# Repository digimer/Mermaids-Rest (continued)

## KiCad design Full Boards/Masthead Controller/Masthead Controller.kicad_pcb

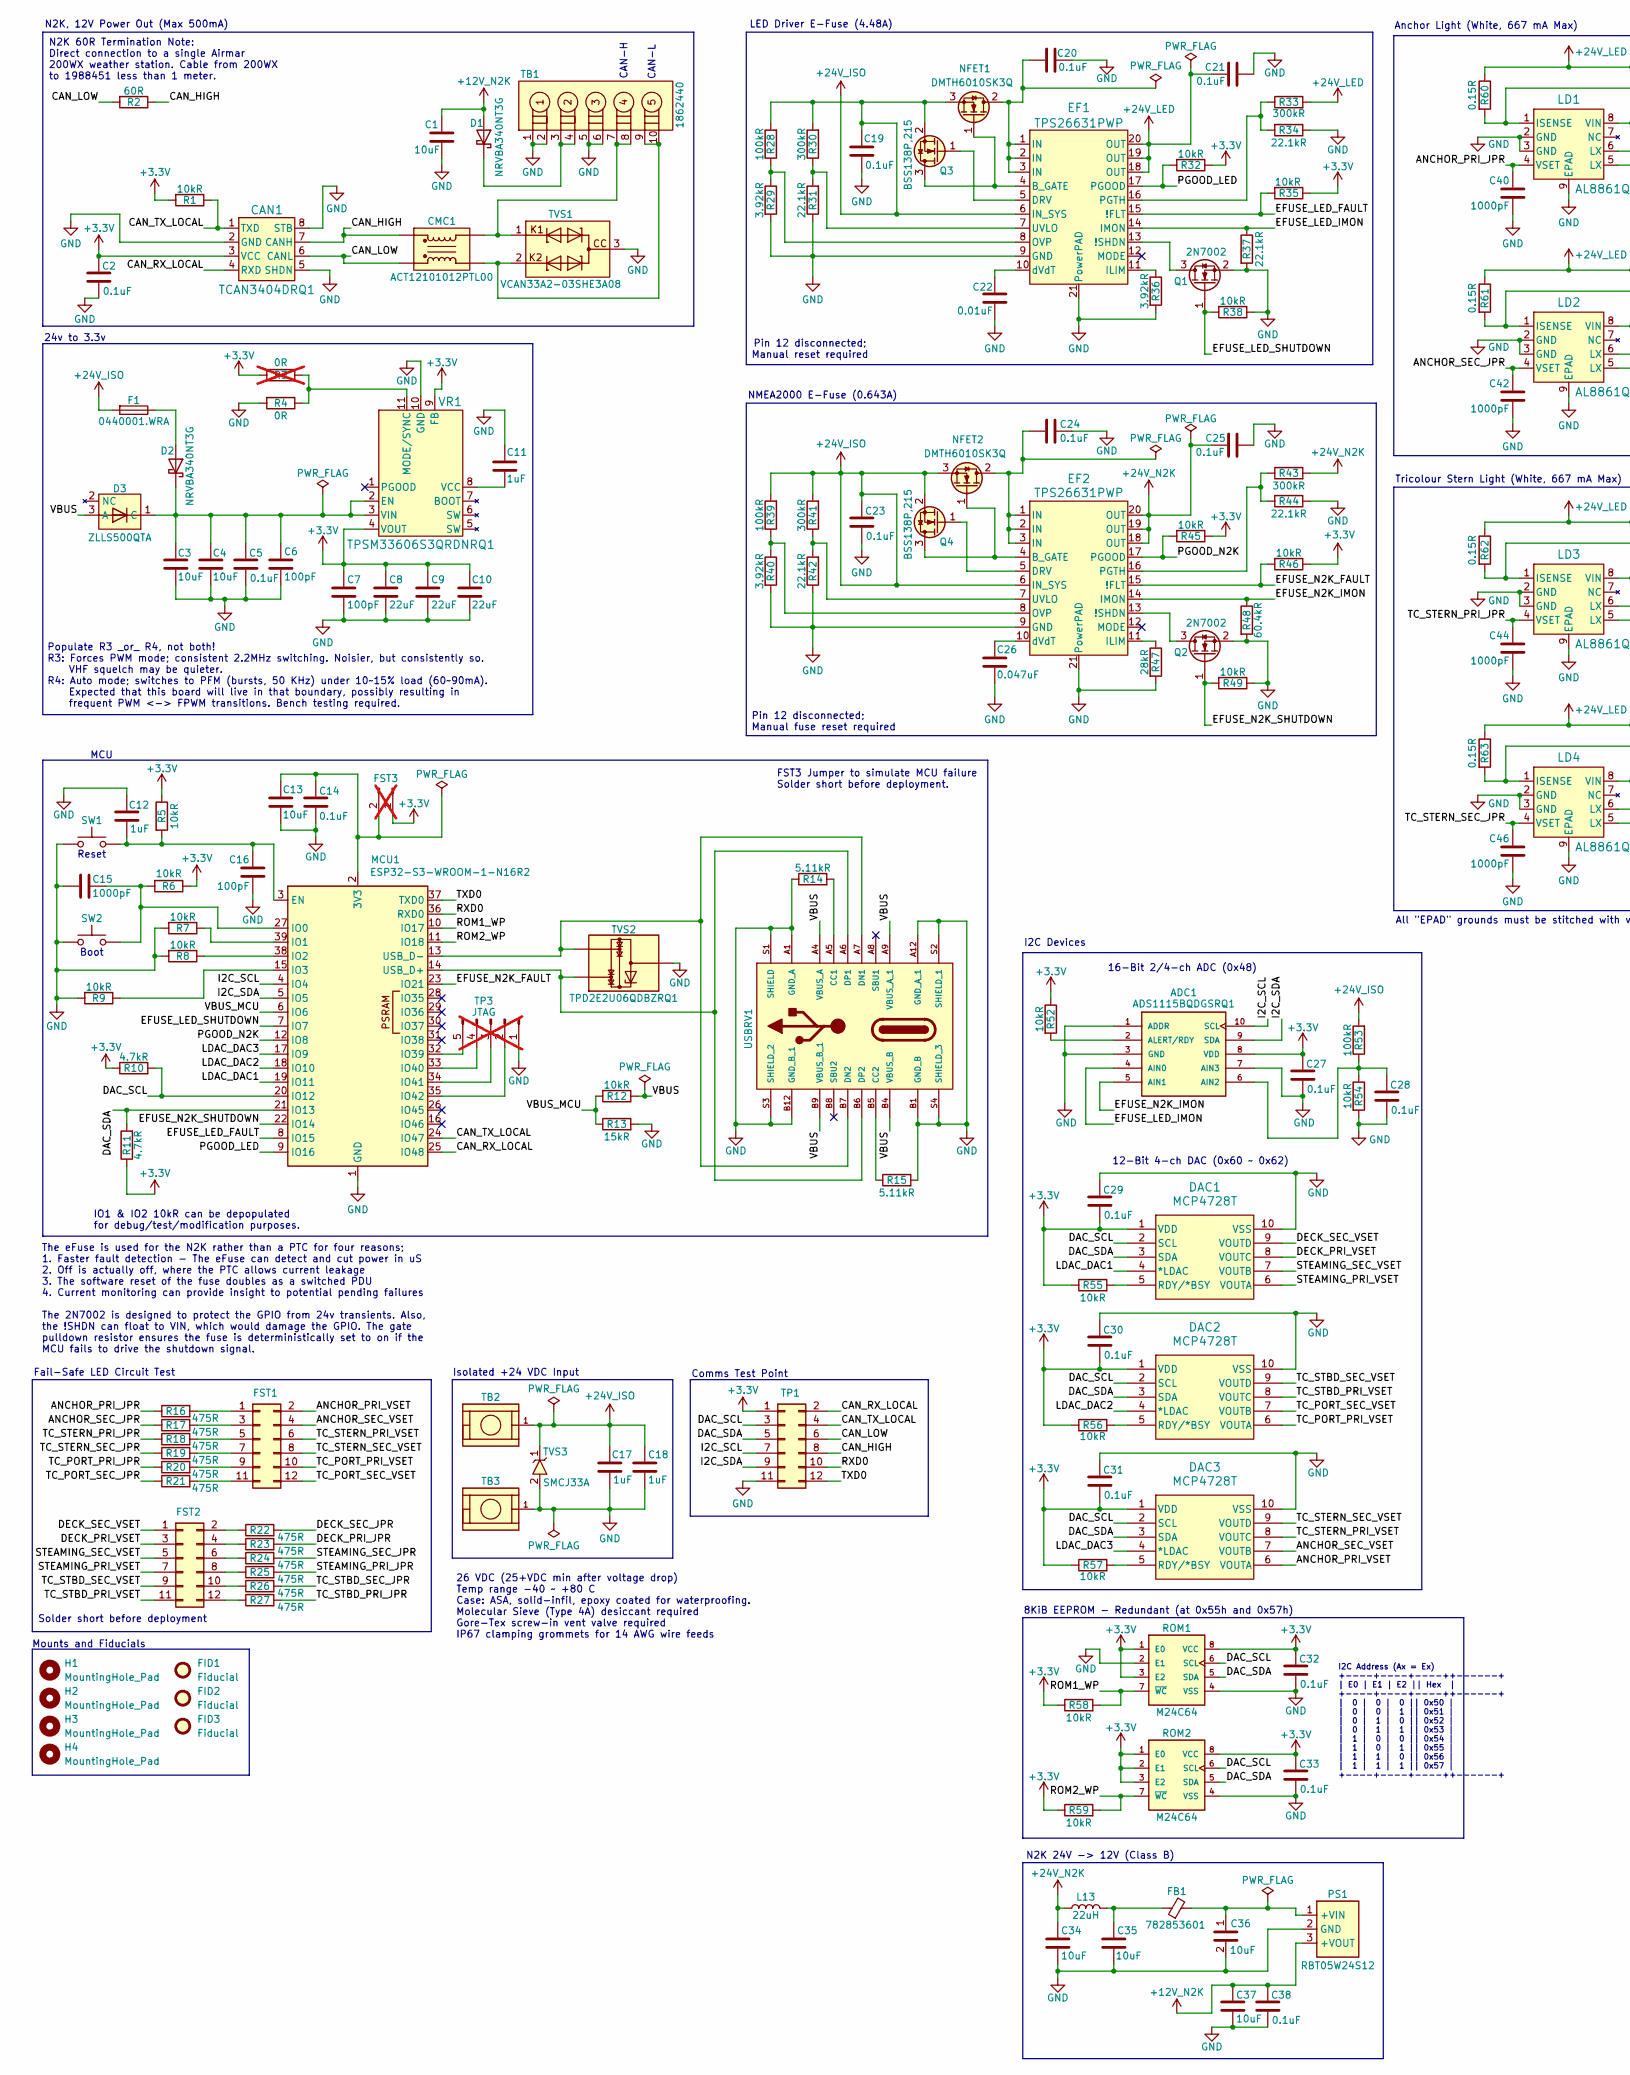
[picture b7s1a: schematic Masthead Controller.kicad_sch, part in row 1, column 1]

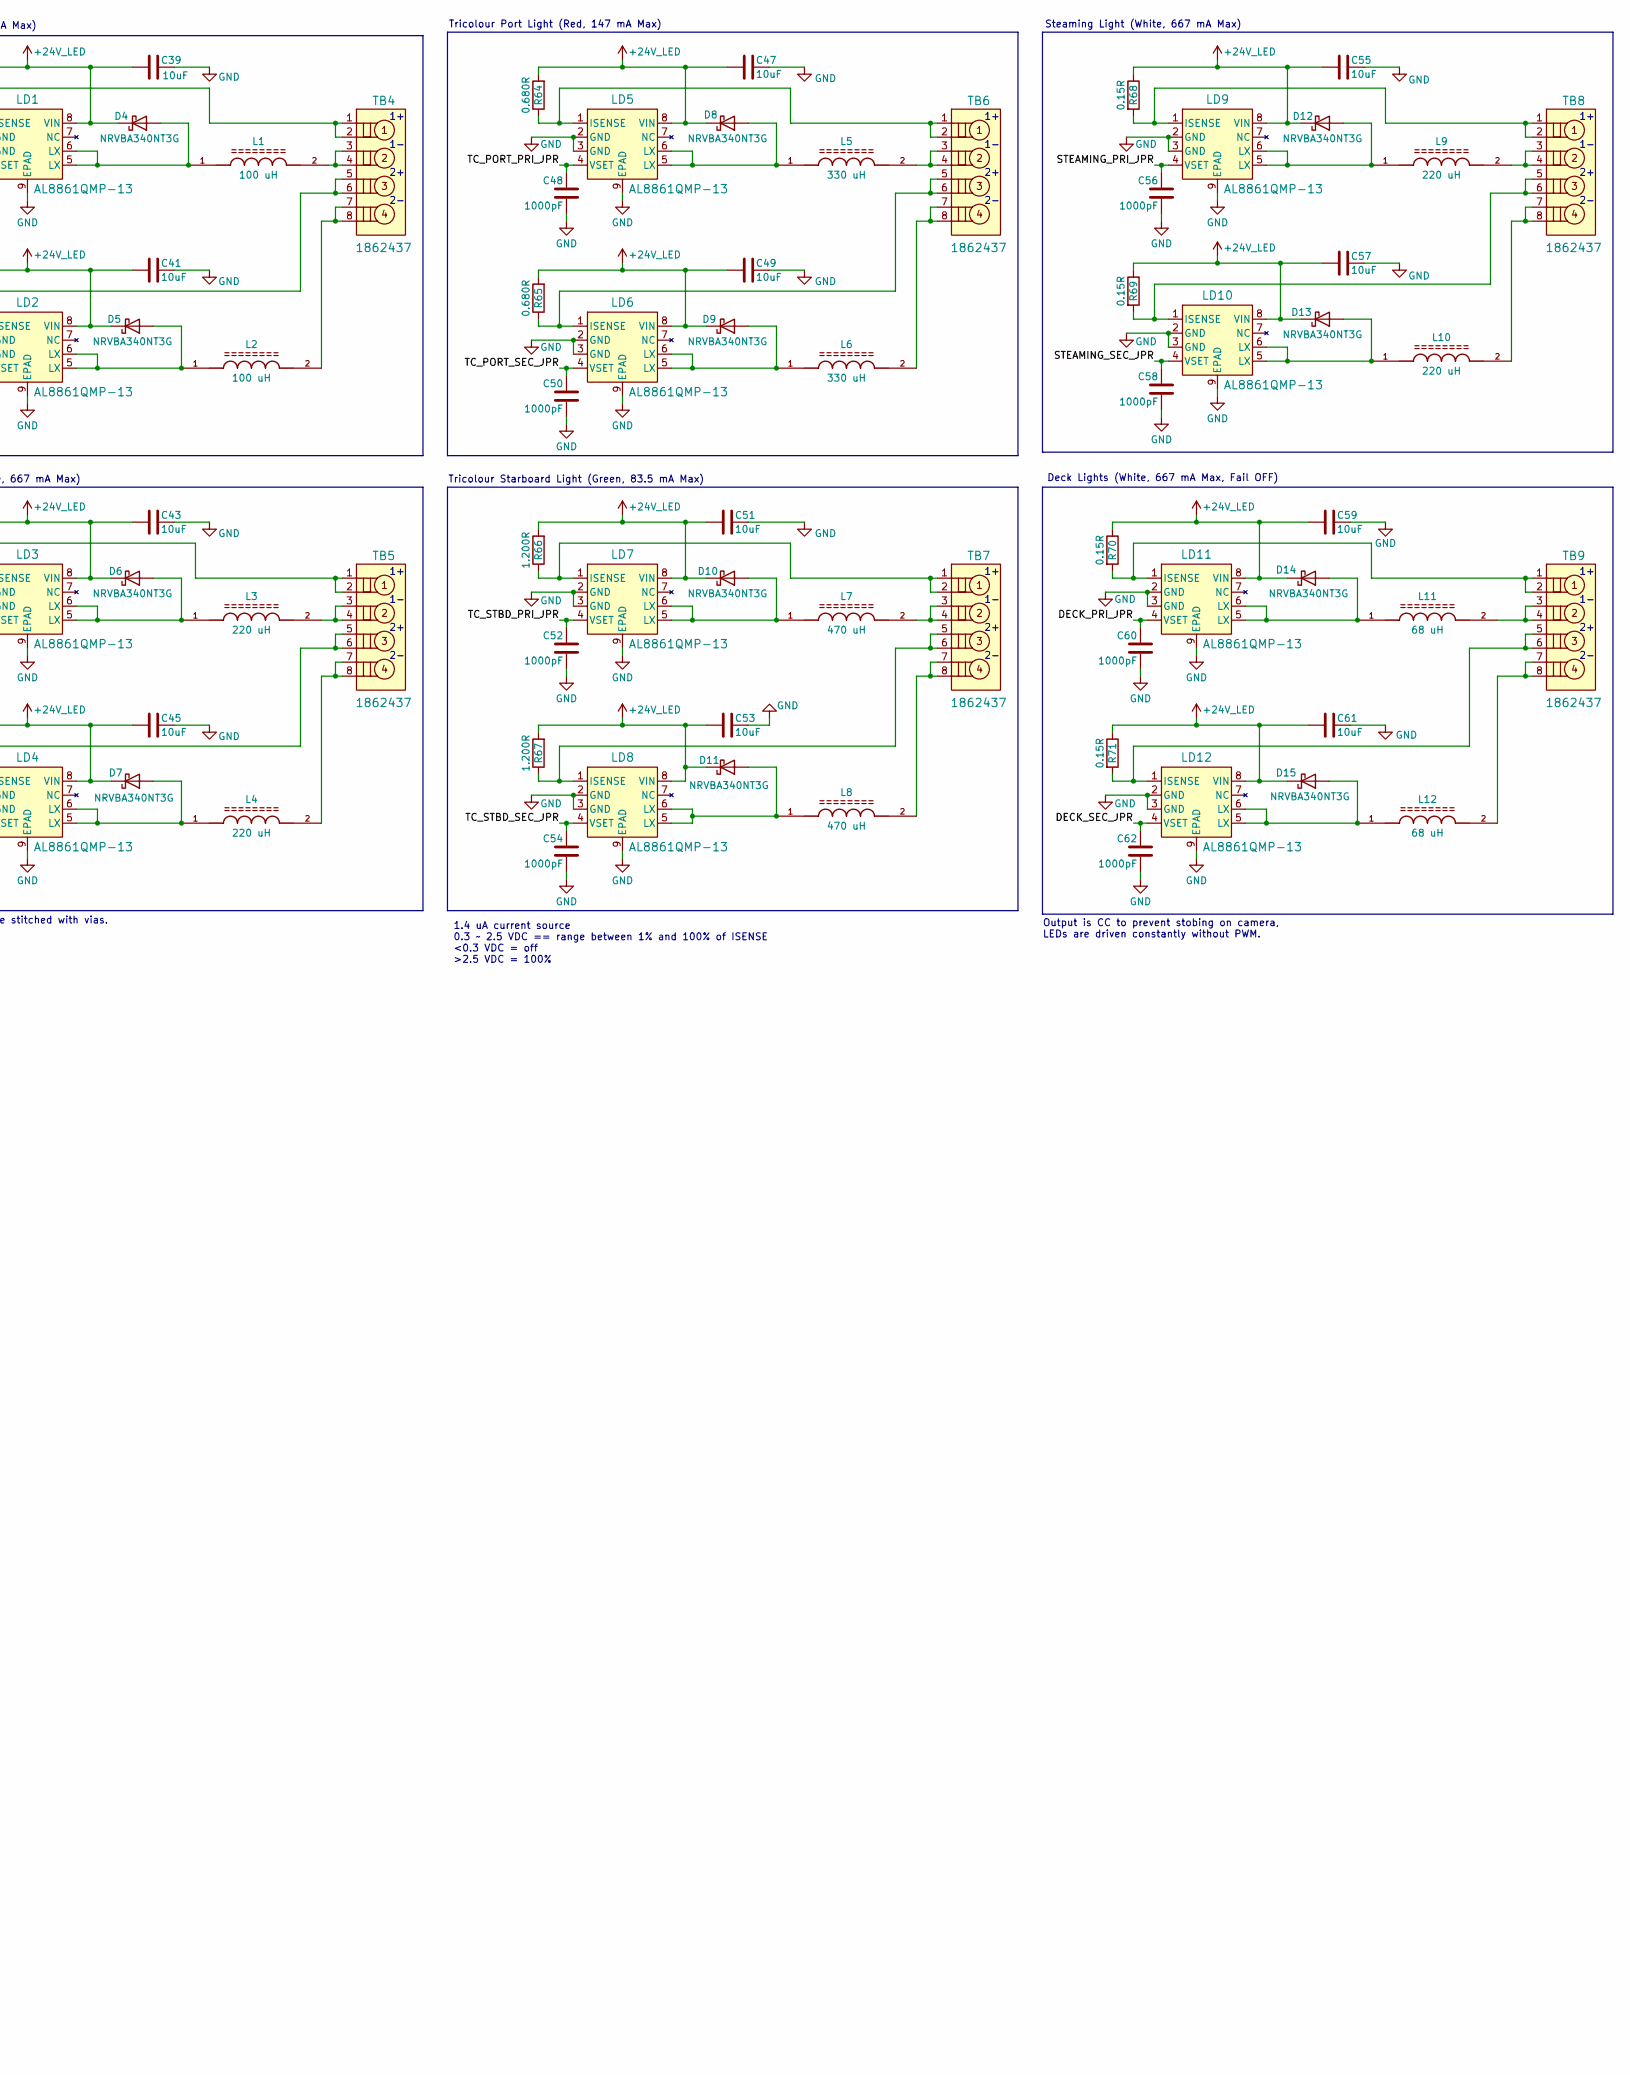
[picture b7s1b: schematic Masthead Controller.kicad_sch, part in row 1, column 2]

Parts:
ADC1: ADS1115BQDGSRQ1; TI ADS1115BQDGSRQ1; Part TI ADS1115BQDGSRQ1
C1, C3, C4, C13, C34, C35, C36, C37, C39, C41, C43, C45, C47, C49, C51, C53, C55, C57, C59, C61: 10uF; TDK CGA5; Part TDK CGA5L1X7R1H106K160AE
C2, C5, C14, C19, C20, C21, C23, C24, C25, C27, C28, C29, C30, C31, C32, C33, C38: 0.1uF; Kyocera AVX 0805; Part Kyocera 08051C104K4Z2A
C6, C7, C16: 100pF; Kemet C0805X; Part Kemet C0805X101J5GACAUTO
C8, C9, C10: 22uF; Murata GCJ32ER71C; Part Murata GCJ32ER71C226KE01L
C11, C12, C17, C18: 1uF; Kyocera AVX 0805; Part Kyocera 08051C105K4Z2A
C15, C40, C42, C44, C46, C48, C50, C52, C54, C56, C58, C60, C62: 1000pF; Kyocera AVX 0805; Part Kyocera 08052C102J4Z2A
C22: 0.01uF; Kyocera AVX 0805; Part Kyocera 08051C103J4Z2A
C26: 0.047uF; Murata GCJ 0805; Part Murata GCJ21BR72A473KA01L
CAN1: TCAN3404DRQ1; TI TCAN3404; Part TI TCAN3404DRQ1
CMC1: ACT12101012PTL00; TDK ACT12101012PTL00; Part TDK ACT1210-101-2P-TL00
D1, D2, D4, D5, D6, D7, D8, D9, D10, D11, D12, D13, D14, D15: NRVBA340NT3G; Onsemi NRVBA340NT3G; Part Onsemi NRVBA340NT3G
D3: ZLLS500QTA; Diodes Inc ZLLS500; Part Diodes Inc ZLLS500QTA
DAC1, DAC2, DAC3: MCP4728T; MT MCP4728T-E_UN; Part Microchip MCP4728T-E/UN
EF1, EF2: TPS26631PWP; TI_TPS26631PWP; Part TI TPS26631PWPR
F1: 0440001.WRA; Littelfuse 440001; Part Littelfuse 0440001.WRA
FB1: 782853601; Würth 782853601; Part Wurth 782853601
FID1, FID2, FID3: Fiducial; Fiducial_1mm_Mask2mm
FST1, FST2: Conn_02x06_Odd_Even; Amphenol 20021111-00012T4LF; Part Amphenol 20021111-00012T4LF
FST3: Conn_01x02_Pin; PinHeader_1x02_P2.54mm_Vertical; Part Amphenol 68001-416HLF; not fitted
H1, H2, H3, H4: MountingHole_Pad; MountingHole_4.3mm_M4_with_Keepout
L1, L2: 100 uH; Bourns SRN6045TA; Part Bourns SRN6045TA-101M
L3, L4, L9, L10: 220 uH; Bourns SRN6045TA; Part Bourns SRN6045TA-221M
L5, L6: 330 uH; Bourns SRN6045TA; Part Bourns SRN6045TA-331K
L7, L8: 470 uH; Bourns SRN6045TA; Part Bourns SRN6045TA-471K
L11, L12: 68 uH; Bourns SRN6045TA; Part Bourns SRN6045TA-680M
L13: 22uH; Bourns SRN4018BTA; Part Bourns SRN4018BTA-220M
LD1, LD2, LD3, LD4, LD5, LD6, LD7, LD8, LD9, LD10, LD11, LD12: AL8861QMP-13; Diodes Inc AL8861QMP-13; Part Diodes Inc AL8861QMP-13
MCU1: ESP32-S3-WROOM-1-N16R2; ESP32-S3-WROOM-1; Part Espressif ESP32-S3-WROOM-1-N16R2
NFET1, NFET2: DMTH6010SK3Q; Diodes Inc DMTH6010SK3Q; Part Diodes Inc DMTH6010SK3Q-13
PS1: RBT05W24S12; XP Power RBT05W; Part XP Power RBT05W
Q1, Q2: 2N7002; SOT-23; Part Diodes Inc 2N7002Q-7-F
Q3, Q4: BSS138P,215; Nexperia BSS138P,215; Part Nexperia BSS138P,215
R1, R5, R6, R7, R8, R9, R12, R32, R35, R38, R45, R46, R49, R52, R54, R55, R56, R57, R58, R59: 10kR; Stackpole RNCP0805; Part Stackpole RNCP0805FTD10K0
R2: 60R; R_Axial_DIN0204_L3.6mm_D1.6mm_P5.08mm_Horizontal; Part Vishay MBA02040C6009FC100
R3: 0R; Vishay RCA-SR e3; Part Vishay RCA08050000ZSEASR; not fitted
R4: 0R; Vishay RCA-SR e3; Part Vishay RCA08050000ZSEASR
R10, R11: 4.7kR; Stackpole RMCA0805; Part Stackpole RMCA0805FT4K70-HP
R13: 15kR; Stackpole RMCA0805; Part Stackpole RMCA0805FT15K0-HP
R14, R15: 5.11kR; Stackpole RNCP0805; Part Stackpole RNCP0805FTD5K11
R16, R17, R18, R19, R20, R21, R22, R23, R24, R25, R26, R27: 475R; Stackpole RNCP0805; Part Stackpole RNCP0805FTD475R
R28, R39, R53: 100kR; Stackpole RMCA0805; Part Stackpole RMCA0805FT100K-HP
R29, R36, R40: 3.92kR; Stackpole RNCP0805; Part Stackpole RNCP0805FTD3K92
R30, R33, R41, R43: 300kR; Yageo AE0805; Part Yageo AE0805BR-07300KL
R31, R34, R37, R42, R44: 22.1kR; Stackpole RNCP0805; Part Stackpole RNCP0805FTD22K1
R47: 28kR; Stackpole RNCP0805; Part Stackpole RNCP0805FTD28K0
R48: 60.4kR; Vishay RCA-SR e3; Part Vishay RCA080560K4FKEA
R60, R61, R62, R63, R68, R69, R70, R71: 0.15R; Vishay RCWE0805; Part Vishay RCWE0805R150FKEA
R64, R65: 0.680R; Vishay RCWE0805; Part Vishay RCWE0805R680FKEA
R66, R67: 1.200R; Panasonic ERJ-UP6 0805; Part Panasonic ERJ-UP6F1R20V
ROM1, ROM2: M24C64; STM M24C64-RMN6P; Part STM M24C64-RMN6P
SW1, SW2: SW_MEC_5G; SW_TS03-66-50-BK-160-LCR-D-67; Part Same Sky TS03-66-50-BK-160-LCR-D-67
TB1: 1862440; Phoenix Contact 1862440; Part Phoenix Contact 1862440
TB2, TB3: 7799; Keystone 7799; Part Keystone 7799
TB4, TB5, TB6, TB7, TB8, TB9: 1862437; Phoenix Contact 1862437; Part Phoenix Contact 1862437
TP1: Conn_02x06_Odd_Even; Amphenol 20021111-00012T4LF; Part Amphenol 20021111-00012T4LF
TP3: JTAG; PinHeader_1x05_P2.54mm_Vertical; not fitted
TVS1: VCAN33A2-03SHE3A08; Vishay VCAN33A2-03S; Part Vishay VCAN33A2-03SHE3A08
TVS2: TPD2E2U06QDBZRQ1; TI TPD2E2U06; Part TI TPD2E2U06QDBZRQ1
TVS3: SMCJ33A; Littelfuse SMCJ; Part Littelfuse SMCJ33A
USBRV1: USB4145-03-0170-C; GCT USB4145-03-0170-C; Part GCT USB4145-03-0170-C
VR1: TPSM33606S3QRDNRQ1; TI TPSM336; Part TI TPSM33606S3QRDNRQ1

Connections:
+3.3V: ADC1.8 (VDD), C2.1, C7.1, C8.1, C9.1, C10.1, C27.1, C29.2, C30.2, C31.2, C32.1, C33.1, CAN1.3 (VCC), DAC1.1 (VDD), DAC2.1 (VDD), DAC3.1 (VDD), FST3.1, R1.2, R3.1, R5.1, R6.1, R10.1, R11.1, R32.1, R35.1, R45.1, R46.1, R52.1, R55.1, R56.1, R57.1, R58.1, R59.1, ROM1.1 (E0), ROM1.3 (E2), ROM1.8 (VCC), ROM2.1 (E0), ROM2.2 (E1), ROM2.3 (E2), ROM2.8 (VCC), TP1.1, VR1.4 (VOUT), VR1.9 (FB)
+24V_ISO: C17.1, C18.1, C19.1, C23.1, EF1.6 (IN_SYS), EF2.6 (IN_SYS), F1.2, NFET1.3 (S), NFET2.3 (S), Q3.2 (S), Q4.2 (S), R28.2, R30.2, R39.2, R41.2, R53.2, TB2.1, TVS3.1
+24V_LED: C21.1, C39.2, C41.2, C43.2, C45.2, C47.2, C49.2, C51.2, C53.2, C55.2, C57.2, C59.2, C61.2, D4.1 (K), D5.1 (K), D6.1 (K), D7.1 (K), D8.1 (K), D9.1 (K), D10.1 (K), D11.1 (K), D12.1 (K), D13.1 (K), D14.1 (K), D15.1 (K), EF1.18 (OUT), EF1.19 (OUT), EF1.20 (OUT), LD1.8 (VIN), LD2.8 (VIN), LD3.8 (VIN), LD4.8 (VIN), LD5.8 (VIN), LD6.8 (VIN), LD7.8 (VIN), LD8.8 (VIN), LD9.8 (VIN), LD10.8 (VIN), LD11.8 (VIN), LD12.8 (VIN), R33.2, R60.1, R61.1, R62.1, R63.1, R64.2, R65.2, R66.2, R67.2, R68.1, R69.1, R70.1, R71.1
+24V_N2K: C25.2, C34.1, EF2.18 (OUT), EF2.19 (OUT), EF2.20 (OUT), L13.1, R43.2
/ANCHOR_PRI_JPR: C40.2, LD1.4 (VSET), R16.1
/ANCHOR_PRI_VSET: DAC3.6 (VOUTA), FST1.2
/ANCHOR_SEC_JPR: C42.2, LD2.4 (VSET), R17.1
/ANCHOR_SEC_VSET: DAC3.7 (VOUTB), FST1.4
/CAN_HIGH: CAN1.7 (CANH), CMC1.1 (I1), R2.1, TP1.8
/CAN_LOW: CAN1.6 (CANL), CMC1.2 (I2), R2.2, TP1.6
/CAN_RX_LOCAL: CAN1.4 (RXD), MCU1.25 (IO48), TP1.2
/CAN_TX_LOCAL: CAN1.1 (TXD), MCU1.24 (IO47), R1.1, TP1.4
/DAC_SCL: DAC1.2 (SCL), DAC2.2 (SCL), DAC3.2 (SCL), MCU1.20 (IO12), R10.2, ROM1.6 (SCL), ROM2.6 (SCL), TP1.3
/DAC_SDA: DAC1.3 (SDA), DAC2.3 (SDA), DAC3.3 (SDA), MCU1.21 (IO13), R11.2, ROM1.5 (SDA), ROM2.5 (SDA), TP1.5
/DECK_PRI_JPR: C60.2, LD11.4 (VSET), R23.2
/DECK_PRI_VSET: DAC1.8 (VOUTC), FST2.3
/DECK_SEC_JPR: C62.2, LD12.4 (VSET), R22.2
/DECK_SEC_VSET: DAC1.9 (VOUTD), FST2.1
/EFUSE_LED_FAULT: EF1.15 (!FLT), MCU1.8 (IO15), R35.2
/EFUSE_LED_IMON: ADC1.4 (AIN0), EF1.14 (IMON), R37.1
/EFUSE_LED_SHUTDOWN: MCU1.7 (IO7), Q1.1 (G), R38.2
/EFUSE_N2K_FAULT: EF2.15 (!FLT), MCU1.23 (IO21), R46.2
/EFUSE_N2K_IMON: ADC1.5 (AIN1), EF2.14 (IMON), R48.1
/EFUSE_N2K_SHUTDOWN: MCU1.22 (IO14), Q2.1 (G), R49.2
/I2C_SCL: ADC1.10 (SCL), MCU1.4 (IO4), TP1.7
/I2C_SDA: ADC1.9 (SDA), MCU1.5 (IO5), TP1.9
/LDAC_DAC1: DAC1.4 (*LDAC), MCU1.19 (IO11)
/LDAC_DAC2: DAC2.4 (*LDAC), MCU1.18 (IO10)
/LDAC_DAC3: DAC3.4 (*LDAC), MCU1.17 (IO9)
/PGOOD_LED: EF1.17 (PGOOD), MCU1.9 (IO16), R32.2
/PGOOD_N2K: EF2.17 (PGOOD), MCU1.12 (IO8), R45.2
/ROM1_WP: MCU1.10 (IO17), R58.2, ROM1.7 (~WC)
/ROM2_WP: MCU1.11 (IO18), R59.2, ROM2.7 (~WC)
/RXD0: MCU1.36 (RXD0), TP1.10
/STEAMING_PRI_JPR: C56.2, LD9.4 (VSET), R25.2
/STEAMING_PRI_VSET: DAC1.6 (VOUTA), FST2.7
/STEAMING_SEC_JPR: C58.2, LD10.4 (VSET), R24.2
/STEAMING_SEC_VSET: DAC1.7 (VOUTB), FST2.5
/TC_PORT_PRI_JPR: C48.2, LD5.4 (VSET), R20.1
/TC_PORT_PRI_VSET: DAC2.6 (VOUTA), FST1.10
/TC_PORT_SEC_JPR: C50.2, LD6.4 (VSET), R21.1
/TC_PORT_SEC_VSET: DAC2.7 (VOUTB), FST1.12
/TC_STBD_PRI_JPR: C52.2, LD7.4 (VSET), R27.2
/TC_STBD_PRI_VSET: DAC2.8 (VOUTC), FST2.11
/TC_STBD_SEC_JPR: C54.2, LD8.4 (VSET), R26.2
/TC_STBD_SEC_VSET: DAC2.9 (VOUTD), FST2.9
/TC_STERN_PRI_JPR: C44.2, LD3.4 (VSET), R18.1
/TC_STERN_PRI_VSET: DAC3.8 (VOUTC), FST1.6
/TC_STERN_SEC_JPR: C46.2, LD4.4 (VSET), R19.1
/TC_STERN_SEC_VSET: DAC3.9 (VOUTD), FST1.8
/TXD0: MCU1.37 (TXD0), TP1.12
/VBUS: D3.3 (A), R12.1, USBRV1.A4 (VBUS_A), USBRV1.A9 (VBUS_A_1), USBRV1.B4 (VBUS_B), USBRV1.B9 (VBUS_B_1)
/VBUS_MCU: MCU1.6 (IO6), R12.2, R13.1
GND: ADC1.1 (ADDR), ADC1.3 (GND), ADC1.7 (AIN3), C1.1, C2.2, C3.2, C4.2, C5.2, C6.2, C7.2, C8.2, C9.2, C10.2, C11.1, C12.1, C13.2, C14.2, C15.2, C16.1, C17.2, C18.2, C19.2, C20.1, C21.2, C22.1, C23.2, C24.1, C25.1, C26.2, C27.2, C28.2, C29.1, C30.1, C31.1, C32.2, C33.2, C34.2, C35.2, C36.2, C37.2, C38.2, C39.1, C40.1, C41.1, C42.1, C43.1, C44.1, C45.1, C46.1, C47.1, C48.1, C49.1, C50.1, C51.1, C52.1, C53.1, C54.1, C55.1, C56.1, C57.1, C58.1, C59.1, C60.1, C61.1, C62.1, CAN1.2 (GND), CAN1.5 (SHDN), CAN1.8 (STB), DAC1.10 (VSS), DAC2.10 (VSS), DAC3.10 (VSS), EF1.9 (GND), EF1.21 (PowerPAD), EF2.9 (GND), EF2.21 (PowerPAD), LD1.2 (GND), LD1.3 (GND), LD1.9 (EPAD), LD2.2 (GND), LD2.3 (GND), LD2.9 (EPAD), LD3.2 (GND), LD3.3 (GND), LD3.9 (EPAD), LD4.2 (GND), LD4.3 (GND), LD4.9 (EPAD), LD5.2 (GND), LD5.3 (GND), LD5.9 (EPAD), LD6.2 (GND), LD6.3 (GND), LD6.9 (EPAD), LD7.2 (GND), LD7.3 (GND), LD7.9 (EPAD), LD8.2 (GND), LD8.3 (GND), LD8.9 (EPAD), LD9.2 (GND), LD9.3 (GND), LD9.9 (EPAD), LD10.2 (GND), LD10.3 (GND), LD10.9 (EPAD), LD11.2 (GND), LD11.3 (GND), LD11.9 (EPAD), LD12.2 (GND), LD12.3 (GND), LD12.9 (EPAD), MCU1.1 (GND), MCU1.40 (GND), MCU1.41 (GND), PS1.2 (GND), Q1.2 (S), Q2.2 (S), R4.2, R7.2, R8.2, R9.2, R13.2, R14.1, R15.2, R29.2, R31.1, R34.1, R36.2, R37.2, R38.1, R40.2, R42.1, R44.1, R47.2, R48.2, R49.1, R54.2, ROM1.2 (E1), ROM1.4 (VSS), ROM2.4 (VSS), SW1.1 (A), SW1.2 (A), SW2.1 (A), SW2.2 (A), TB1.1, TB1.2, TB1.5, TB1.6, TB3.1, TP1.11, TP3.1, TVS1.3, TVS2.3 (GND), TVS3.2, USBRV1.A1 (GND_A), USBRV1.A12 (GND_A_1), USBRV1.B1 (GND_B), USBRV1.B12 (GND_B_1), USBRV1.S1 (SHIELD), USBRV1.S2 (SHIELD_1), USBRV1.S3 (SHIELD_2), USBRV1.S4 (SHIELD_3), VR1.10 (GND)
unnamed: ADC1.6 (AIN2), C28.1, R53.1, R54.1
unnamed: ADC1.2 (ALERT/RDY), R52.2
unnamed: C35.1, FB1.1, L13.2
unnamed: CMC1.4 (O1), TB1.7, TB1.8, TVS1.1
unnamed: CMC1.3 (O2), TB1.9, TB1.10, TVS1.2
unnamed: D2.2 (A), F1.1
unnamed: C3.1, C4.1, C5.1, C6.1, D2.1 (K), D3.1 (C), VR1.2 (EN), VR1.3 (VIN)
unnamed: D4.2 (A), L1.1, LD1.5 (LX), LD1.6 (LX)
unnamed: D5.2 (A), L2.1, LD2.5 (LX), LD2.6 (LX)
unnamed: D6.2 (A), L3.1, LD3.5 (LX), LD3.6 (LX)
unnamed: D7.2 (A), L4.1, LD4.5 (LX), LD4.6 (LX)
unnamed: D8.2 (A), L5.1, LD5.5 (LX), LD5.6 (LX)
unnamed: D9.2 (A), L6.1, LD6.5 (LX), LD6.6 (LX)
unnamed: D10.2 (A), L7.1, LD7.5 (LX), LD7.6 (LX)
unnamed: D11.2 (A), L8.1, LD8.5 (LX), LD8.6 (LX)
unnamed: D12.2 (A), L9.1, LD9.5 (LX), LD9.6 (LX)
unnamed: D13.2 (A), L10.1, LD10.5 (LX), LD10.6 (LX)
unnamed: D14.2 (A), L11.1, LD11.5 (LX), LD11.6 (LX)
unnamed: D15.2 (A), L12.1, LD12.5 (LX), LD12.6 (LX)
unnamed: DAC1.5 (RDY/*BSY), R55.2
unnamed: DAC2.5 (RDY/*BSY), R56.2
unnamed: DAC3.5 (RDY/*BSY), R57.2
unnamed: EF1.13 (!SHDN), Q1.3 (D)
unnamed: EF1.4 (B_GATE), NFET1.1 (G), Q3.3 (D)
unnamed: EF1.5 (DRV), Q3.1 (G)
unnamed: EF1.11 (ILIM), R36.1
unnamed: EF1.8 (OVP), R28.1, R29.1
unnamed: EF1.16 (PGTH), R33.1, R34.2
unnamed: EF1.7 (UVLO), R30.1, R31.2
unnamed: C22.2, EF1.10 (dVdT)
unnamed: EF2.13 (!SHDN), Q2.3 (D)
unnamed: EF2.4 (B_GATE), NFET2.1 (G), Q4.3 (D)
unnamed: EF2.5 (DRV), Q4.1 (G)
unnamed: EF2.11 (ILIM), R47.1
unnamed: EF2.8 (OVP), R39.1, R40.1
unnamed: EF2.16 (PGTH), R43.1, R44.2
unnamed: EF2.7 (UVLO), R41.1, R42.2
unnamed: C26.1, EF2.10 (dVdT)
unnamed: FST1.1, R16.2
unnamed: FST1.3, R17.2
unnamed: FST1.5, R18.2
unnamed: FST1.7, R19.2
unnamed: FST1.9, R20.2
unnamed: FST1.11, R21.2
unnamed: FST2.2, R22.1
unnamed: FST2.4, R23.1
unnamed: FST2.6, R24.1
unnamed: FST2.8, R25.1
unnamed: FST2.10, R26.1
unnamed: FST2.12, R27.1
unnamed: C13.1, C14.1, FST3.2, MCU1.2 (3V3)
unnamed: L1.2, TB4.3, TB4.4
unnamed: L2.2, TB4.7, TB4.8
unnamed: L3.2, TB5.3, TB5.4
unnamed: L4.2, TB5.7, TB5.8
unnamed: L5.2, TB6.3, TB6.4
unnamed: L6.2, TB6.7, TB6.8
unnamed: L7.2, TB7.3, TB7.4
unnamed: L8.2, TB7.7, TB7.8
unnamed: L9.2, TB8.3, TB8.4
unnamed: L10.2, TB8.7, TB8.8
unnamed: L11.2, TB9.3, TB9.4
unnamed: L12.2, TB9.7, TB9.8
unnamed: LD1.1 (ISENSE), R60.2, TB4.1, TB4.2
unnamed: LD2.1 (ISENSE), R61.2, TB4.5, TB4.6
unnamed: LD3.1 (ISENSE), R62.2, TB5.1, TB5.2
unnamed: LD4.1 (ISENSE), R63.2, TB5.5, TB5.6
unnamed: LD5.1 (ISENSE), R64.1, TB6.1, TB6.2
unnamed: LD6.1 (ISENSE), R65.1, TB6.5, TB6.6
unnamed: LD7.1 (ISENSE), R66.1, TB7.1, TB7.2
unnamed: LD8.1 (ISENSE), R67.1, TB7.5, TB7.6
unnamed: LD9.1 (ISENSE), R68.2, TB8.1, TB8.2
unnamed: LD10.1 (ISENSE), R69.2, TB8.5, TB8.6
unnamed: LD11.1 (ISENSE), R70.2, TB9.1, TB9.2
unnamed: LD12.1 (ISENSE), R71.2, TB9.5, TB9.6
unnamed: C12.2, C16.2, MCU1.3 (EN), R5.2, SW1.3 (B), SW1.4 (B)
unnamed: C15.1, MCU1.27 (IO0), R6.2, SW2.3 (B), SW2.4 (B)
unnamed: MCU1.39 (IO1), R7.1
unnamed: MCU1.38 (IO2), R8.1
unnamed: MCU1.15 (IO3), R9.1
unnamed: MCU1.32 (IO39), TP3.5
unnamed: MCU1.33 (IO40), TP3.4
unnamed: MCU1.34 (IO41), TP3.3
unnamed: MCU1.35 (IO42), TP3.2
unnamed: MCU1.14 (USB_D+), TVS2.1 (IO1), USBRV1.A6 (DP1), USBRV1.B6 (DP2)
unnamed: MCU1.13 (USB_D-), TVS2.2 (IO2), USBRV1.A7 (DN1), USBRV1.B7 (DN2)
unnamed: C20.2, EF1.1 (IN), EF1.2 (IN), EF1.3 (IN), NFET1.2 (D)
unnamed: C24.2, EF2.1 (IN), EF2.2 (IN), EF2.3 (IN), NFET2.2 (D)
unnamed: C36.1, FB1.2, PS1.1 (+VIN)
unnamed: R14.2, USBRV1.A5 (CC1)
unnamed: R15.1, USBRV1.B5 (CC2)
unnamed: R3.2, R4.1, VR1.11 (MODE/SYNC)
unnamed: C11.2, VR1.8 (VCC)

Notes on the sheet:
Boot
Mounts and Fiducials
CAN-H
1.4 uA current source 0.3 ~ 2.5 VDC == range between 1% and 100% of ISENSE <0.3 VDC = off >2.5 VDC = 100%
MCU
The eFuse is used for the N2K rather than a PTC for four reasons; 1. Faster fault detection - The eFuse can detect and cut power in uS 2. Off is actually off, where the PTC allows current leakage 3. The software reset of the fuse doubles as a switched PDU 4. Current monitoring can provide insight t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
Solder short before deployment
Output is CC to prevent stobing on camera, LEDs are driven constantly without PWM.
N2K 24V -> 12V (Class B)
Anchor Light (White, 667 mA Max)
Pin 12 disconnected; Manual fuse reset required
Deck Lights (White, 667 mA Max, Fail OFF)
26 VDC (25+VDC min after voltage drop) Temp range -40 ~ +80 C Case: ASA, solid-infil, epoxy coated for waterproofing. Molecular Sieve (Type 4A) desiccant required Gore-Tex screw-in vent valve required IP67 clamping grommets for 14 AWG wire feeds
Pin 12 disconnected; Manual reset required
All "EPAD" grounds must be stitched with vias.
IO1 & IO2 10kR can be depopulated for debug/test/modification purposes.
FST3 Jumper to simulate MCU failure Solder short before deployment.
Tricolour Stern Light (White, 667 mA Max)
I2C Devices
Reset
CAN-L
Fail-Safe LED Circuit Test
Tricolour Port Light (Red, 147 mA Max)
N2K, 12V Power Out (Max 500mA)
I2C Address (Ax = Ex) +----+----+----++------+ | E0 | E1 | E2 || Hex | +----+----+----++------+ | 0 | 0 | 0 || 0x50 | | 0 | 0 | 1 || 0x51 | | 0 | 1 | 0 || 0x52 | | 0 | 1 | 1 || 0x53 | | 1 | 0 | 0 || 0x54 | | 1 | 0 | 1 || 0x55 | | 1 | 1 | 0 || 0x56 | | 1 | 1 | 1 || 0x57 | +----+----+----++------+
16-Bit 2/4-ch ADC (0x48)
Populate R3 _or_ R4, not both! R3: Forces PWM mode; consistent 2.2MHz switching. Noisier, but consistently so. VHF squelch may be quieter. R4: Auto mode; switches to PFM (bursts, 50 KHz) under 10~15% load (60~90mA). Expected that this board will live in that boundary, possibly resulting in frequent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
Tricolour Starboard Light (Green, 83.5 mA Max)
Isolated +24 VDC Input
LED Driver E-Fuse (4.48A)
Comms Test Point
24v to 3.3v
Steaming Light (White, 667 mA Max)
NMEA2000 E-Fuse (0.643A)
12-Bit 4-ch DAC (0x60 ~ 0x62)
8KiB EEPROM - Redundant (at 0x55h and 0x57h)
N2K 60R Termination Note: Direct connection to a single Airmar 200WX weather station. Cable from 200WX to 1988451 less than 1 meter.

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
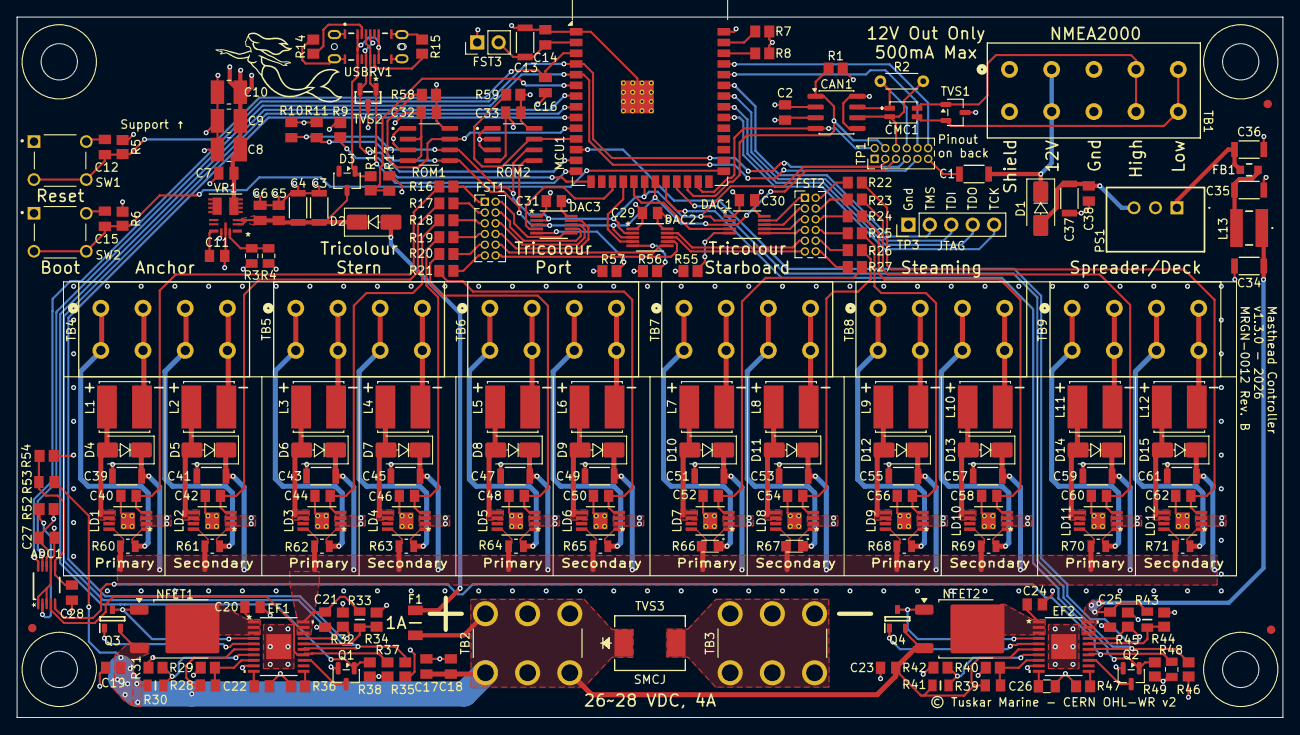
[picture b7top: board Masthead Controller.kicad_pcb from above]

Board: 4 copper layers, 150.0 x 83.0 mm, 219 parts (0 on the bottom side), 149 nets.
